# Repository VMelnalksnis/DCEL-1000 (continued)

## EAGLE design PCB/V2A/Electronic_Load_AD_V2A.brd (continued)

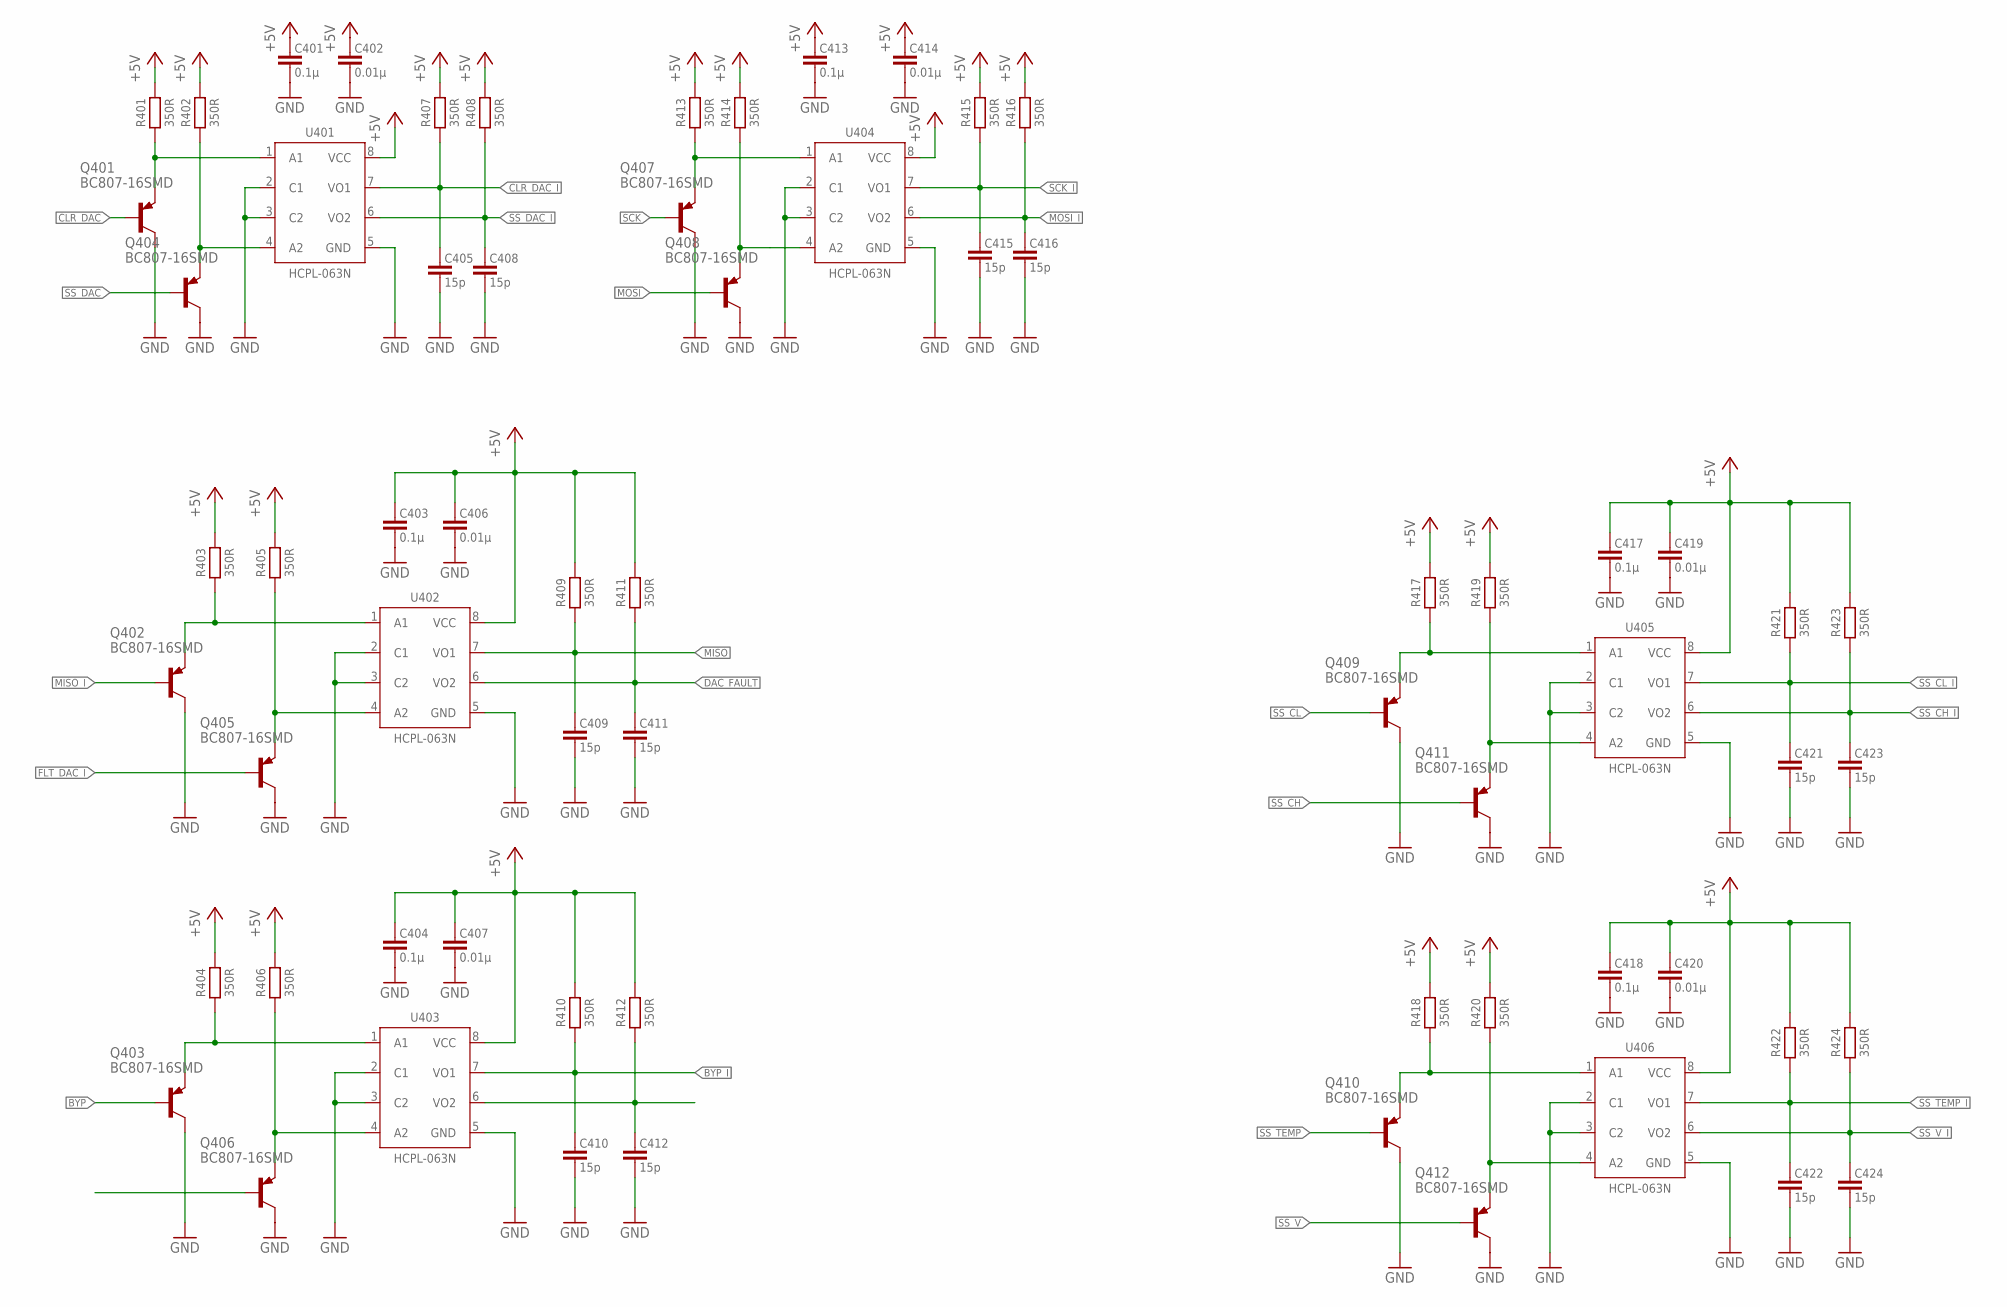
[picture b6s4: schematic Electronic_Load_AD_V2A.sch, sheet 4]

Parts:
C401, C403, C404, C413, C417, C418: 0.1µ; C3216
C402, C406, C407, C414, C419, C420: 0.01µ; C3216
C405, C408, C409, C410, C411, C412, C415, C416, C421, C422, C423, C424: 15p; C1608
Q401, Q402, Q403, Q404, Q405, Q406, Q407, Q408, Q409, Q410, Q411, Q412: BC807-16SMD; SOT23-BEC
R401, R402, R403, R404, R405, R406, R407, R408, R409, R410, R411, R412, R413, R414, R415, R416, R417, R418, R419, R420, R421, R422, R423, R424: 350R; R1608
U401, U402, U403, U404, U405, U406: HCPL-063N; SO8

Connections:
+5V: C401.1, C402.1, C403.1, C404.1, C406.1, C407.1, C413.1, C414.1, C417.1, C418.1, C419.1, C420.1, R401.2, R402.2, R403.2, R404.2, R405.2, R406.2, R407.2, R408.2, R409.2, R410.2, R411.2, R412.2, R413.2, R414.2, R415.2, R416.2, R417.2, R418.2, R419.2, R420.2, R421.2, R422.2, R423.2, R424.2, U401.8 (VCC), U402.8 (VCC), U403.8 (VCC), U404.8 (VCC), U405.8 (VCC), U406.8 (VCC); also elsewhere on the board
BYP: Q403.B
BYP_I: C410.1, R410.1, U403.7 (VO1); also elsewhere on the board
CLR_DAC: Q401.B
CLR_DAC_I: C405.1, R407.1, U401.7 (VO1); also elsewhere on the board
DAC_FAULT: C411.1, R411.1, U402.6 (VO2)
FLT_DAC_I: Q405.B; also elsewhere on the board
GND: C401.2, C402.2, C403.2, C404.2, C405.2, C406.2, C407.2, C408.2, C409.2, C410.2, C411.2, C412.2, C413.2, C414.2, C415.2, C416.2, C417.2, C418.2, C419.2, C420.2, C421.2, C422.2, C423.2, C424.2, Q401.C, Q402.C, Q403.C, Q404.C, Q405.C, Q406.C, Q407.C, Q408.C, Q409.C, Q410.C, Q411.C, Q412.C, U401.2 (C1), U401.3 (C2), U401.5 (GND), U402.2 (C1), U402.3 (C2), U402.5 (GND), U403.2 (C1), U403.3 (C2), U403.5 (GND), U404.2 (C1), U404.3 (C2), U404.5 (GND), U405.2 (C1), U405.3 (C2), U405.5 (GND), U406.2 (C1), U406.3 (C2), U406.5 (GND); also elsewhere on the board
MISO: C409.1, R409.1, U402.7 (VO1)
MISO_I: Q402.B; also elsewhere on the board
MOSI: Q408.B
MOSI_I: C416.1, R416.1, U404.6 (VO2); also elsewhere on the board
unnamed: Q407.E, R413.1, U404.1 (A1)
unnamed: Q409.E, R417.1, U405.1 (A1)
unnamed: Q408.E, R414.1, U404.4 (A2)
unnamed: Q411.E, R419.1, U405.4 (A2)
unnamed: Q410.E, R418.1, U406.1 (A1)
unnamed: Q412.E, R420.1, U406.4 (A2)
unnamed: Q402.E, R403.1, U402.1 (A1)
unnamed: Q405.E, R405.1, U402.4 (A2)
unnamed: Q403.E, R404.1, U403.1 (A1)
unnamed: Q406.E, R406.1, U403.4 (A2)
unnamed: C412.1, R412.1, U403.6 (VO2)
unnamed: Q401.E, R401.1, U401.1 (A1)
unnamed: Q404.E, R402.1, U401.4 (A2)
SCK: Q407.B
SCK_I: C415.1, R415.1, U404.7 (VO1); also elsewhere on the board
SS_CH: Q411.B
SS_CH_I: C423.1, R423.1, U405.6 (VO2); also elsewhere on the board
SS_CL: Q409.B
SS_CL_I: C421.1, R421.1, U405.7 (VO1); also elsewhere on the board
SS_DAC: Q404.B
SS_DAC_I: C408.1, R408.1, U401.6 (VO2); also elsewhere on the board
SS_TEMP: Q410.B
SS_TEMP_I: C422.1, R422.1, U406.7 (VO1); also elsewhere on the board
SS_V: Q412.B
SS_V_I: C424.1, R424.1, U406.6 (VO2); also elsewhere on the board

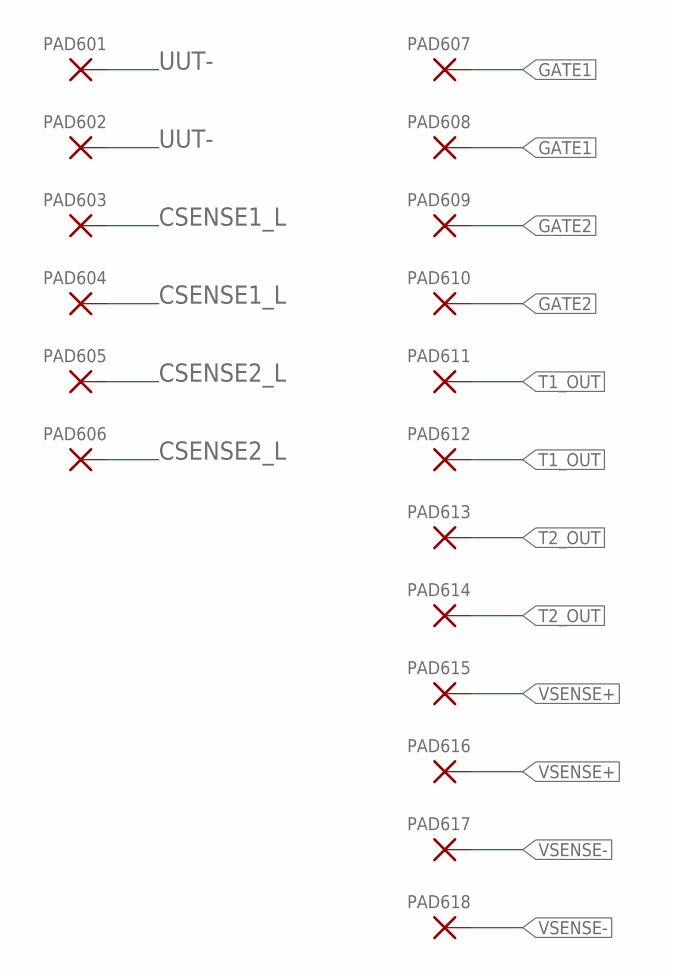
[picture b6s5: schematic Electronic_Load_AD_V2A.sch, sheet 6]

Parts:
PAD601, PAD602, PAD603, PAD604, PAD605, PAD606: PAD-10X4
PAD607, PAD608, PAD609, PAD610, PAD611, PAD612, PAD613, PAD614, PAD615, PAD616, PAD617, PAD618: PAD-5X2

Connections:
CSENSE1_L: PAD603.1, PAD604.1; also elsewhere on the board
CSENSE2_L: PAD605.1, PAD606.1; also elsewhere on the board
GATE1: PAD607.1, PAD608.1; also elsewhere on the board
GATE2: PAD609.1, PAD610.1; also elsewhere on the board
T1_OUT: PAD611.1, PAD612.1; also elsewhere on the board
T2_OUT: PAD613.1, PAD614.1; also elsewhere on the board
UUT-: PAD601.1, PAD602.1; also elsewhere on the board
VSENSE+: PAD615.1, PAD616.1; also elsewhere on the board
VSENSE-: PAD617.1, PAD618.1; also elsewhere on the board

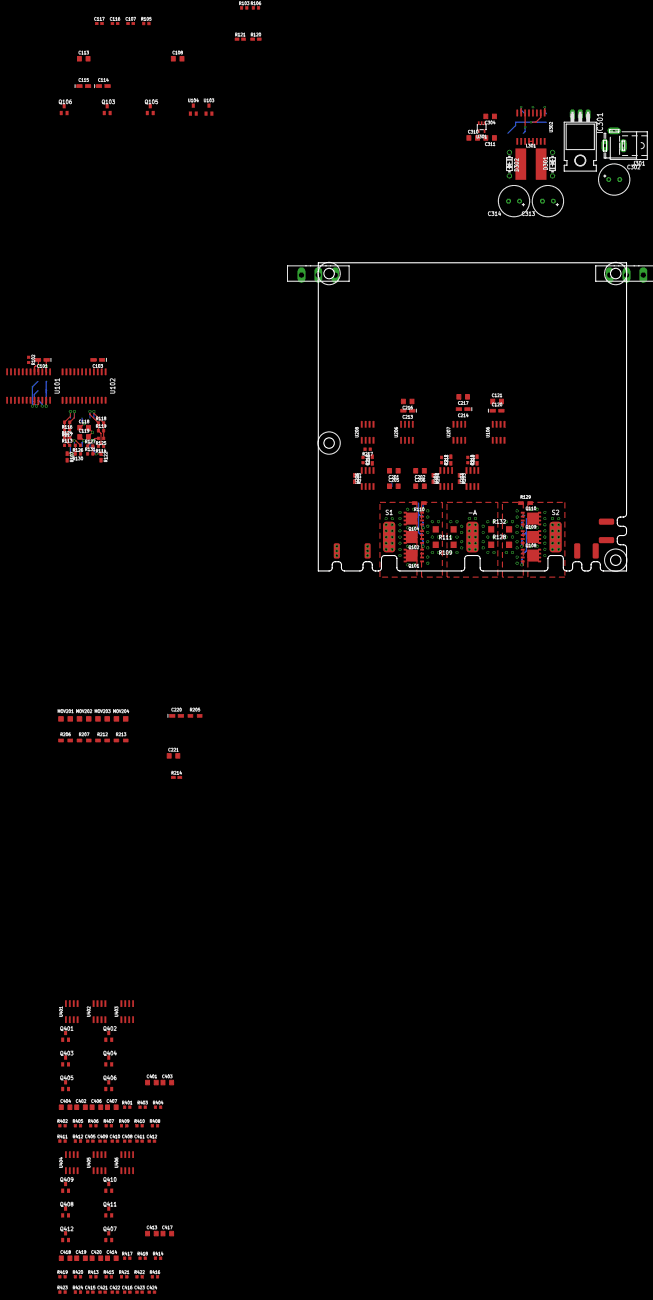
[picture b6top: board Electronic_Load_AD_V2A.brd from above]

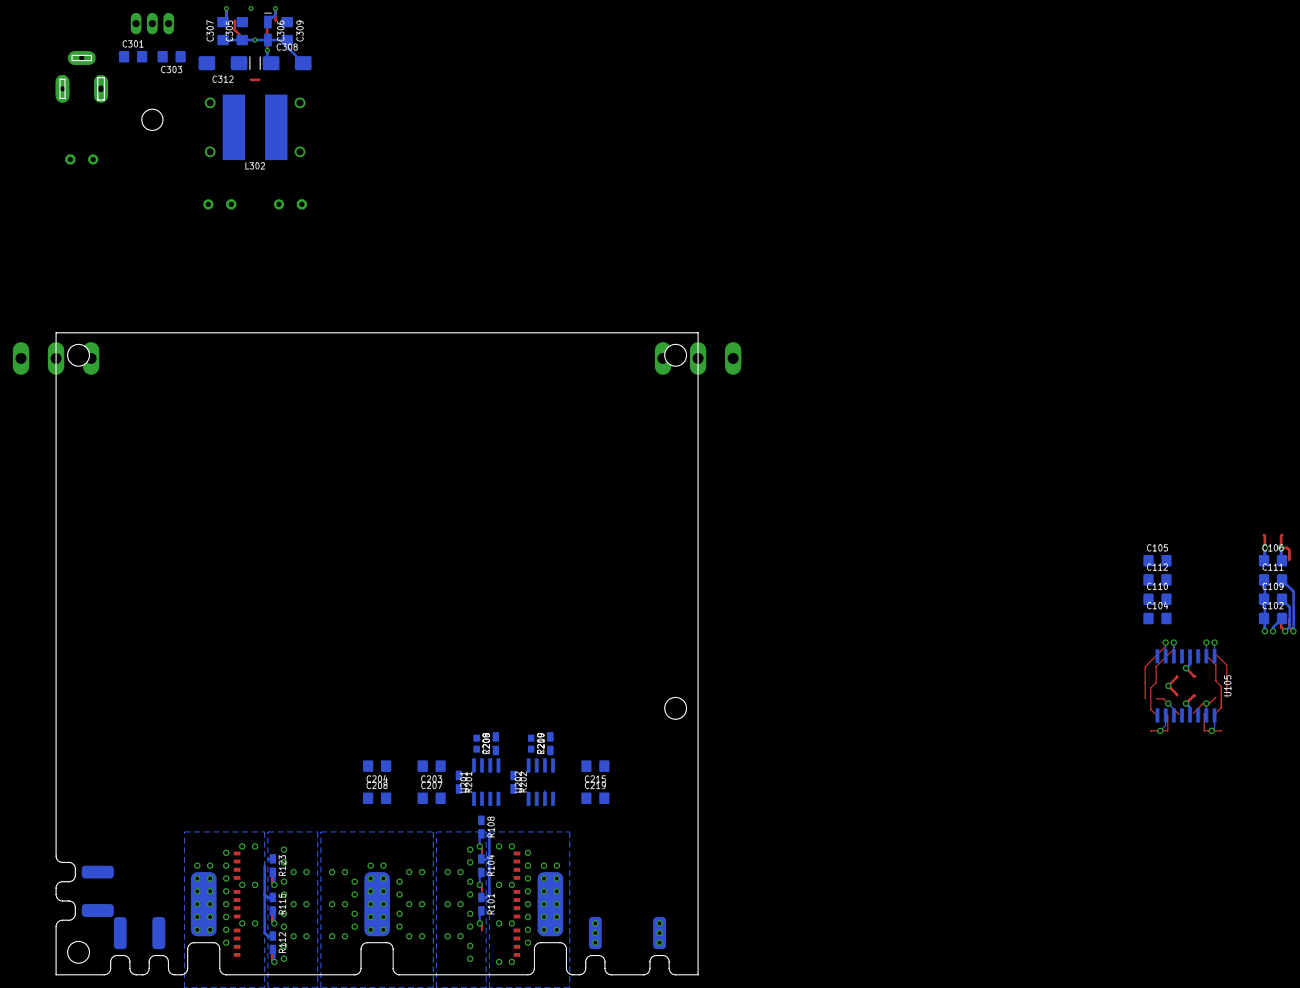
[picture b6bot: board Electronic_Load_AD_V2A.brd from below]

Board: 4 copper layers, 230 parts (47 on the bottom side), 107 nets.

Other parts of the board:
U$1, U$2, U$3, U$4: M3

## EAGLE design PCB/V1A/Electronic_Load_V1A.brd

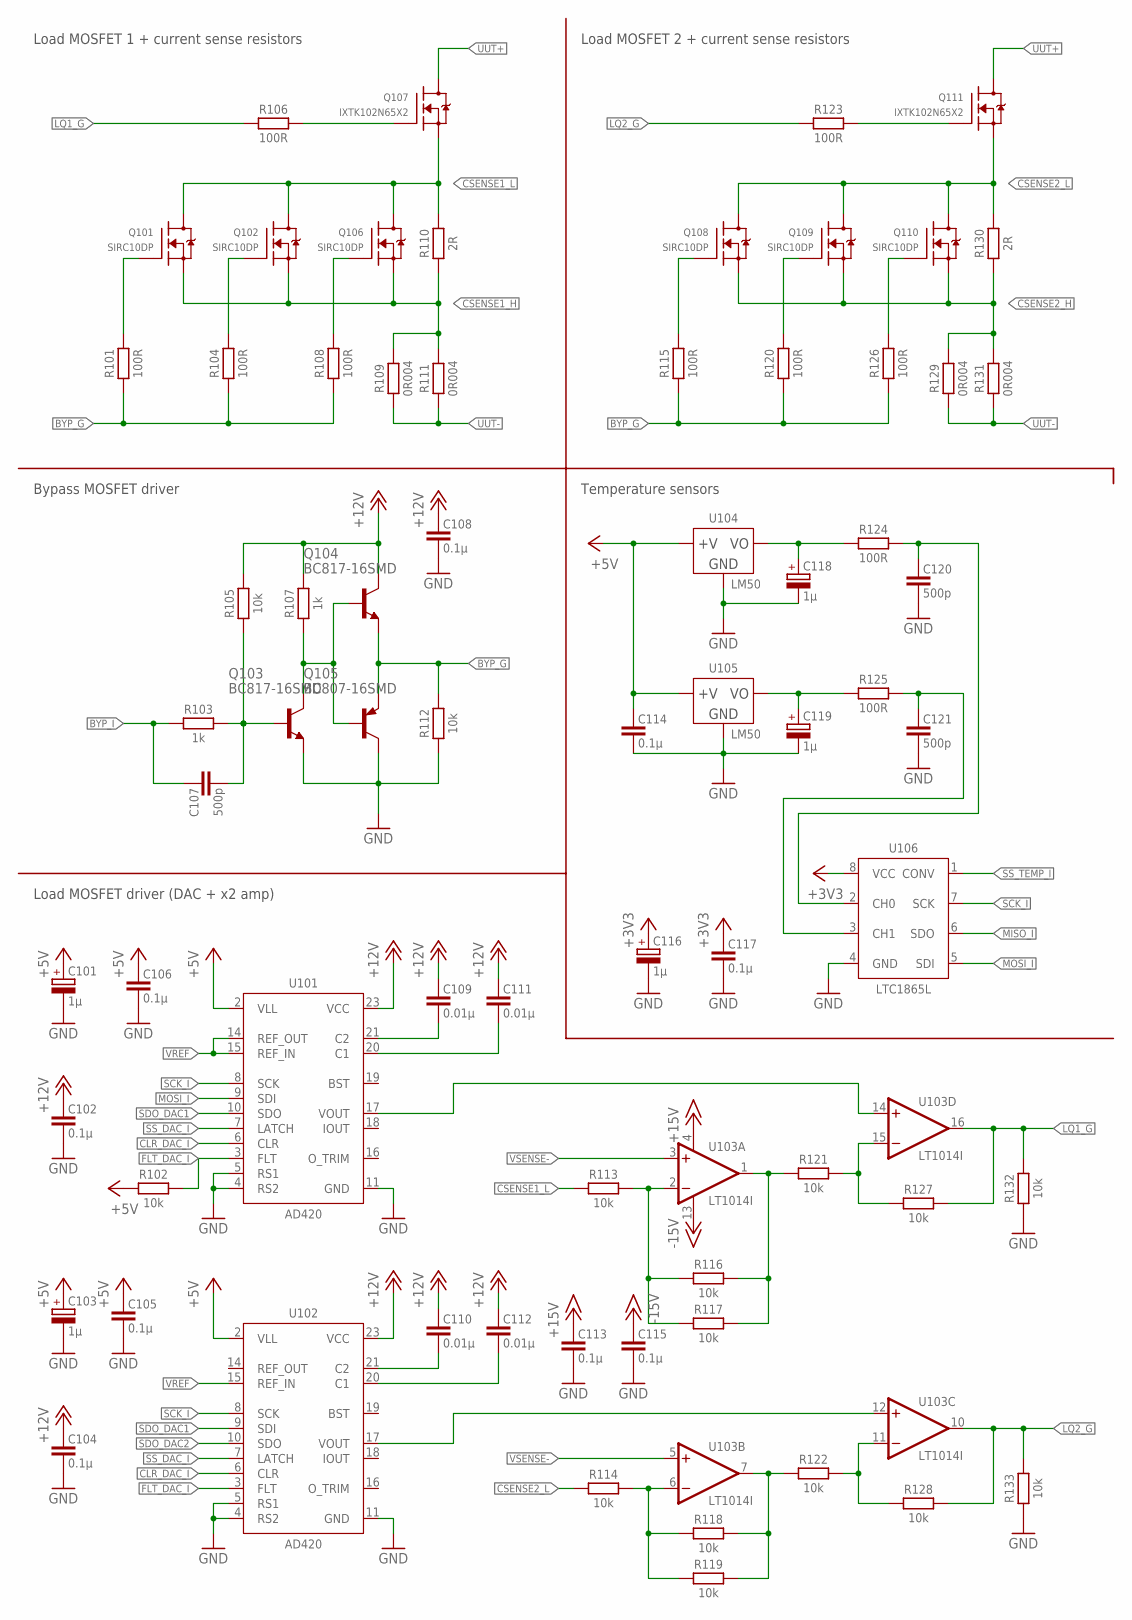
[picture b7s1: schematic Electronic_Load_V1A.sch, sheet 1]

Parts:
C101, C103, C116, C118, C119: 1µ; CT3216
C102, C104, C105, C106, C108, C113, C114, C115, C117: 0.1µ; C3216
C107, C120, C121: 500p; C1608
C109, C110, C111, C112: 0.01µ; C3216
Q101, Q102, Q106, Q108, Q109, Q110: SIRC10DP; POWERPAK-SO-8
Q103, Q104: BC817-16SMD; SOT23-BEC
Q105: BC807-16SMD; SOT23-BEC
R101, R104, R106, R108, R115, R120, R123, R124, R125, R126: 100R; R2012W
R102, R105, R112, R113, R114, R116, R117, R118, R119, R121, R122, R127, R128, R132, R133: 10k; R1608
R103, R107: 1k; R1608
R109, R111, R129, R131: 0R004; R6332W
R110, R130: 2R; R3216W
U101, U102: AD420; SO24W
U103: LT1014I; SO16W
U106: LTC1865L; SO8

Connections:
+3V3: C116.+, C117.1, U106.8 (VCC); also elsewhere on the board
+5V: C101.+, C103.+, C105.1, C106.1, C114.1, R102.1, U101.2 (VLL), U102.2 (VLL); also elsewhere on the board
+12V: C102.1, C104.1, C108.1, C109.1, C110.1, C111.1, C112.1, Q104.C, R105.2, R107.2, U101.23 (VCC), U102.23 (VCC); also elsewhere on the board
+15V: C113.1, U103.4 (V+); also elsewhere on the board
-15V: C115.1, U103.13 (V-); also elsewhere on the board
BYP_G: Q104.E, Q105.E, R101.1, R104.1, R108.1, R112.2, R115.1, R120.1, R126.1
BYP_I: C107.1, R103.1; also elsewhere on the board
CLR_DAC_I: U101.6 (CLR), U102.6 (CLR); also elsewhere on the board
CSENSE1_H: Q101.1 (S), Q101.2 (S), Q101.3 (S), Q102.1 (S), Q102.2 (S), Q102.3 (S), Q106.1 (S), Q106.2 (S), Q106.3 (S), R109.2, R110.1, R111.2; also elsewhere on the board
CSENSE1_L: Q101.5 (D), Q102.5 (D), Q106.5 (D), R110.2, R113.1; also elsewhere on the board
CSENSE2_H: Q108.1 (S), Q108.2 (S), Q108.3 (S), Q109.1 (S), Q109.2 (S), Q109.3 (S), Q110.1 (S), Q110.2 (S), Q110.3 (S), R129.2, R130.1, R131.2; also elsewhere on the board
CSENSE2_L: Q108.5 (D), Q109.5 (D), Q110.5 (D), R114.1, R130.2; also elsewhere on the board
FLT_DAC_I: R102.2, U101.3 (FLT), U102.3 (FLT); also elsewhere on the board
GATE1: R106.2; also elsewhere on the board
GATE2: R123.2; also elsewhere on the board
GND: C101.-, C102.2, C103.-, C104.2, C105.2, C106.2, C108.2, C113.2, C114.2, C115.2, C116.-, C117.2, C118.-, C119.-, C120.2, C121.2, Q103.E, Q105.C, R112.1, R132.1, R133.1, U101.4 (RS2), U101.5 (RS1), U101.11 (GND), U102.4 (RS2), U102.5 (RS1), U102.11 (GND), U106.4 (GND); also elsewhere on the board
LBQ11_G: Q101.4 (G), R101.2
LBQ12_G: Q102.4 (G), R104.2
LBQ13_G: Q106.4 (G), R108.2
LBQ21_G: Q108.4 (G), R115.2
LBQ22_G: Q109.4 (G), R120.2
LBQ23_G: Q110.4 (G), R126.2
LQ1_G: R106.1, R127.2, R132.2, U103.16 (OUT)
LQ2_G: R123.1, R128.2, R133.2, U103.10 (OUT)
MISO_I: U106.6 (SDO); also elsewhere on the board
MOSI_I: U101.9 (SDI), U106.5 (SDI); also elsewhere on the board
unnamed: C109.2, U101.21 (C2)
unnamed: C111.2, U101.20 (C1)
unnamed: Q103.C, Q104.B, Q105.B, R107.1
unnamed: C110.2, U102.21 (C2)
unnamed: C112.2, U102.20 (C1)
unnamed: C107.2, Q103.B, R103.2, R105.1
unnamed: R122.2, R128.1, U103.11 (-IN)
unnamed: U101.17 (VOUT), U103.14 (+IN)
unnamed: U102.17 (VOUT), U103.12 (+IN)
unnamed: R121.2, R127.1, U103.15 (-IN)
unnamed: R116.2, R117.2, R121.1, U103.1 (OUT)
unnamed: R113.2, R116.1, R117.1, U103.2 (-IN)
unnamed: R114.2, R118.1, R119.1, U103.6 (-IN)
unnamed: R118.2, R119.2, R122.1, U103.7 (OUT)
SCK_I: U101.8 (SCK), U102.8 (SCK), U106.7 (SCK); also elsewhere on the board
SDO_DAC1: U101.10 (SDO), U102.9 (SDI)
SDO_DAC2: U102.10 (SDO)
SS_DAC_I: U101.7 (LATCH), U102.7 (LATCH); also elsewhere on the board
SS_TEMP_I: U106.1 (CONV); also elsewhere on the board
T1_OUT: C118.+, R124.1; also elsewhere on the board
T2_OUT: C119.+, R125.1; also elsewhere on the board
TEMP1: C120.1, R124.2, U106.2 (CH0)
TEMP2: C121.1, R125.2, U106.3 (CH1)
UUT-: R109.1, R111.1, R129.1, R131.1; also elsewhere on the board
VREF: U101.14 (REF_OUT), U101.15 (REF_IN), U102.15 (REF_IN); also elsewhere on the board
VSENSE-: U103.3 (+IN), U103.5 (+IN); also elsewhere on the board

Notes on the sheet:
Load MOSFET 1 + current sense resistors
Load MOSFET 2 + current sense resistors
Bypass MOSFET driver
Load MOSFET driver (DAC + x2 amp)
Temperature sensors

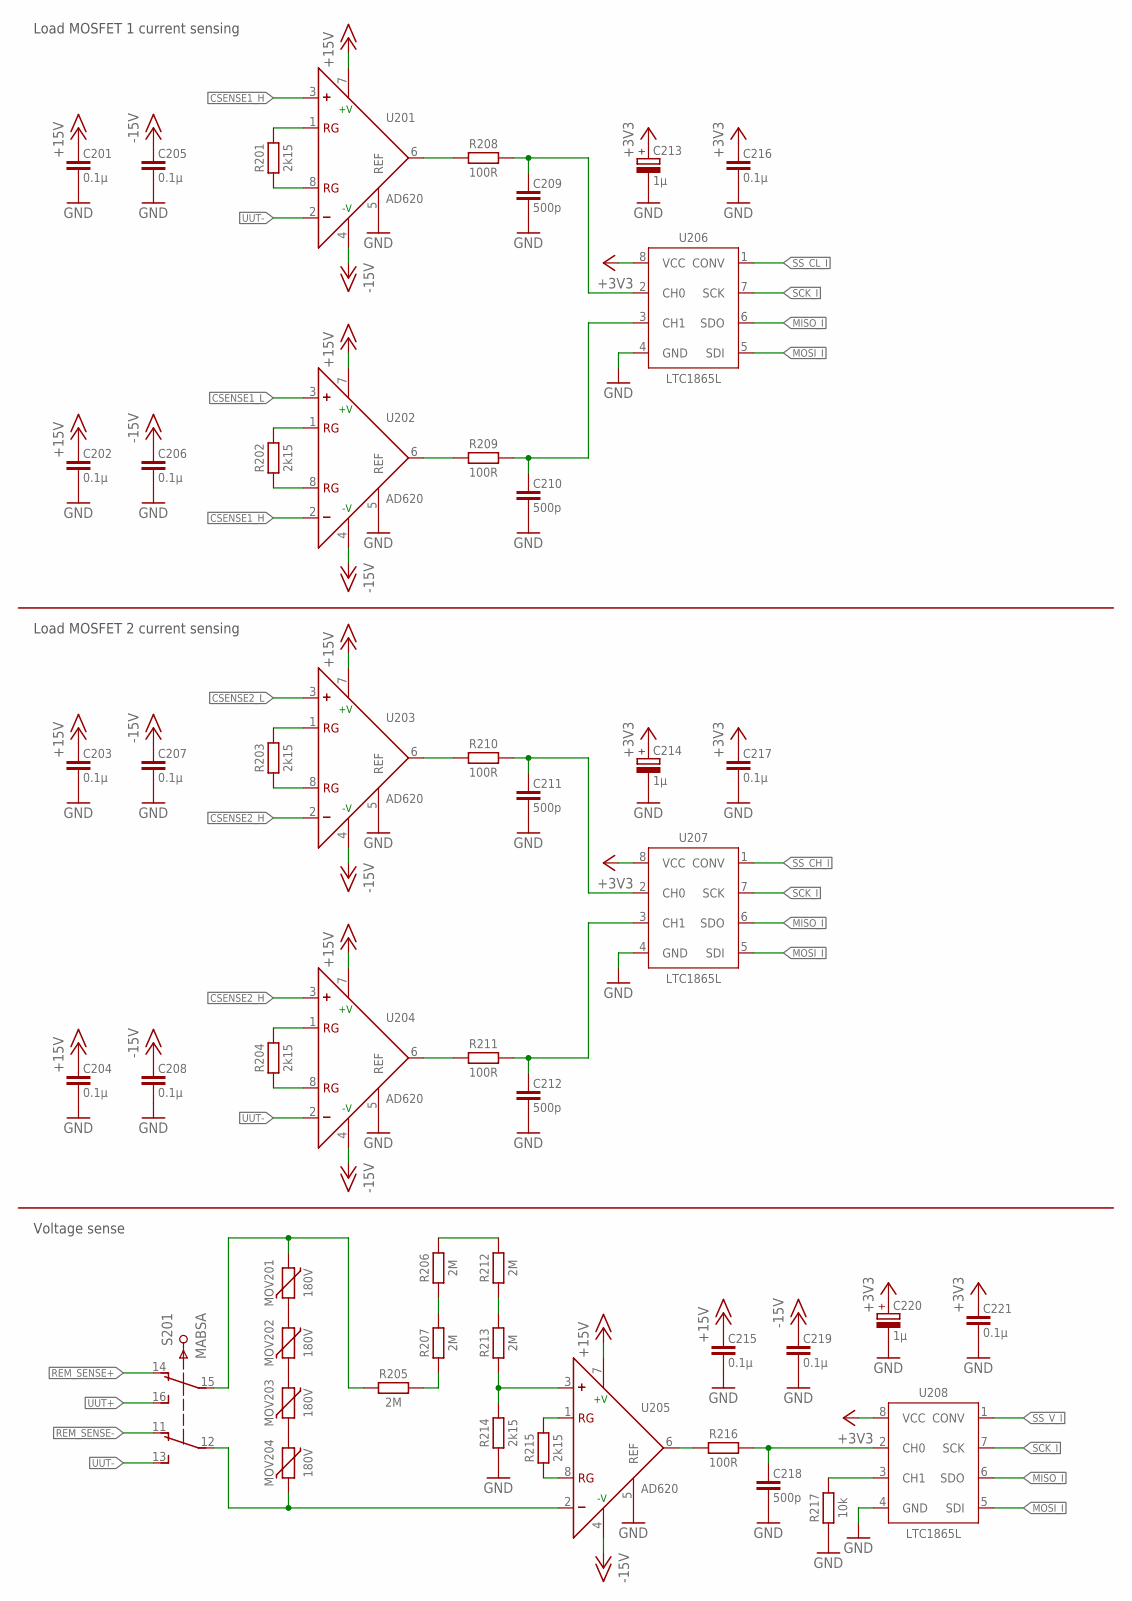
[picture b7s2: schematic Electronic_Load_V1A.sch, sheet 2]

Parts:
C201, C202, C203, C204, C205, C206, C207, C208, C215, C216, C217, C219, C221: 0.1µ; C3216
C209, C210, C211, C212, C218: 500p; C1608
C213, C214, C220: 1µ; CT3216
MOV201, MOV202, MOV203, MOV204: 180V; R3225W
R201, R202, R203, R204, R214, R215: 2k15; R2012W
R205, R206, R207, R212, R213: 2M; R3216W
R208, R209, R210, R211, R216: 100R; R2012W
R217: 10k; R1608
S201: MABSA
U201, U202, U203, U204, U205: AD620; SO8
U206, U207, U208: LTC1865L; SO8

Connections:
+3V3: C213.+, C214.+, C216.1, C217.1, C220.+, C221.1, U206.8 (VCC), U207.8 (VCC), U208.8 (VCC); also elsewhere on the board
+15V: C201.1, C202.1, C203.1, C204.1, C215.1, U201.7 (+V), U202.7 (+V), U203.7 (+V), U204.7 (+V), U205.7 (+V); also elsewhere on the board
-15V: C205.1, C206.1, C207.1, C208.1, C219.1, U201.4 (-V), U202.4 (-V), U203.4 (-V), U204.4 (-V), U205.4 (-V); also elsewhere on the board
CSENSE1_H: U201.3 (+), U202.2 (-); also elsewhere on the board
CSENSE1_L: U202.3 (+); also elsewhere on the board
CSENSE2_H: U203.2 (-), U204.3 (+); also elsewhere on the board
CSENSE2_L: U203.3 (+); also elsewhere on the board
GND: C201.2, C202.2, C203.2, C204.2, C205.2, C206.2, C207.2, C208.2, C209.2, C210.2, C211.2, C212.2, C213.-, C214.-, C215.2, C216.2, C217.2, C218.2, C219.2, C220.-, C221.2, R214.1, R217.1, U201.5 (REF), U202.5 (REF), U203.5 (REF), U204.5 (REF), U205.5 (REF), U206.4 (GND), U207.4 (GND), U208.4 (GND); also elsewhere on the board
MISO_I: U206.6 (SDO), U207.6 (SDO), U208.6 (SDO); also elsewhere on the board
MOSI_I: U206.5 (SDI), U207.5 (SDI), U208.5 (SDI); also elsewhere on the board
unnamed: MOV201.2, MOV202.1
unnamed: MOV202.2, MOV203.1
unnamed: R210.1, U203.6 (OUT)
unnamed: C211.1, R210.2, U207.2 (CH0)
unnamed: R211.1, U204.6 (OUT)
unnamed: C212.1, R211.2, U207.3 (CH1)
unnamed: C209.1, R208.2, U206.2 (CH0)
unnamed: C210.1, R209.2, U206.3 (CH1)
unnamed: R209.1, U202.6 (OUT)
unnamed: R208.1, U201.6 (OUT)
unnamed: R212.1, R213.2
unnamed: R206.2, R212.2
unnamed: R206.1, R207.2
unnamed: R205.2, R207.1
unnamed: R213.1, R214.2, U205.3 (+)
unnamed: C218.1, R216.2, U208.2 (CH0)
unnamed: R216.1, U205.6 (OUT)
unnamed: MOV203.2, MOV204.1
unnamed: R217.2, U208.3 (CH1)
REM_SENSE+: S201.14
REM_SENSE-: S201.11
RG1_H4: R203.2, U203.1 (RG)
RG1_H5: R204.2, U204.1 (RG)
RG1_H6: R215.2, U205.1 (RG)
RG1_L3: R201.2, U201.1 (RG)
RG1_L4: R202.2, U202.1 (RG)
RG2_H4: R203.1, U203.8 (RG)
RG2_H5: R204.1, U204.8 (RG)
RG2_H6: R215.1, U205.8 (RG)
RG2_L3: R201.1, U201.8 (RG)
RG2_L4: R202.1, U202.8 (RG)
SCK_I: U206.7 (SCK), U207.7 (SCK), U208.7 (SCK); also elsewhere on the board
SS_CH_I: U207.1 (CONV); also elsewhere on the board
SS_CL_I: U206.1 (CONV); also elsewhere on the board
SS_V_I: U208.1 (CONV); also elsewhere on the board
UUT+: S201.16
UUT-: S201.13, U201.2 (-), U204.2 (-); also elsewhere on the board
VSENSE+: MOV201.1, R205.1, S201.15; also elsewhere on the board
VSENSE-: MOV204.2, S201.12, U205.2 (-); also elsewhere on the board

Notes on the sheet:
Load MOSFET 2 current sensing
Load MOSFET 1 current sensing
Voltage sense

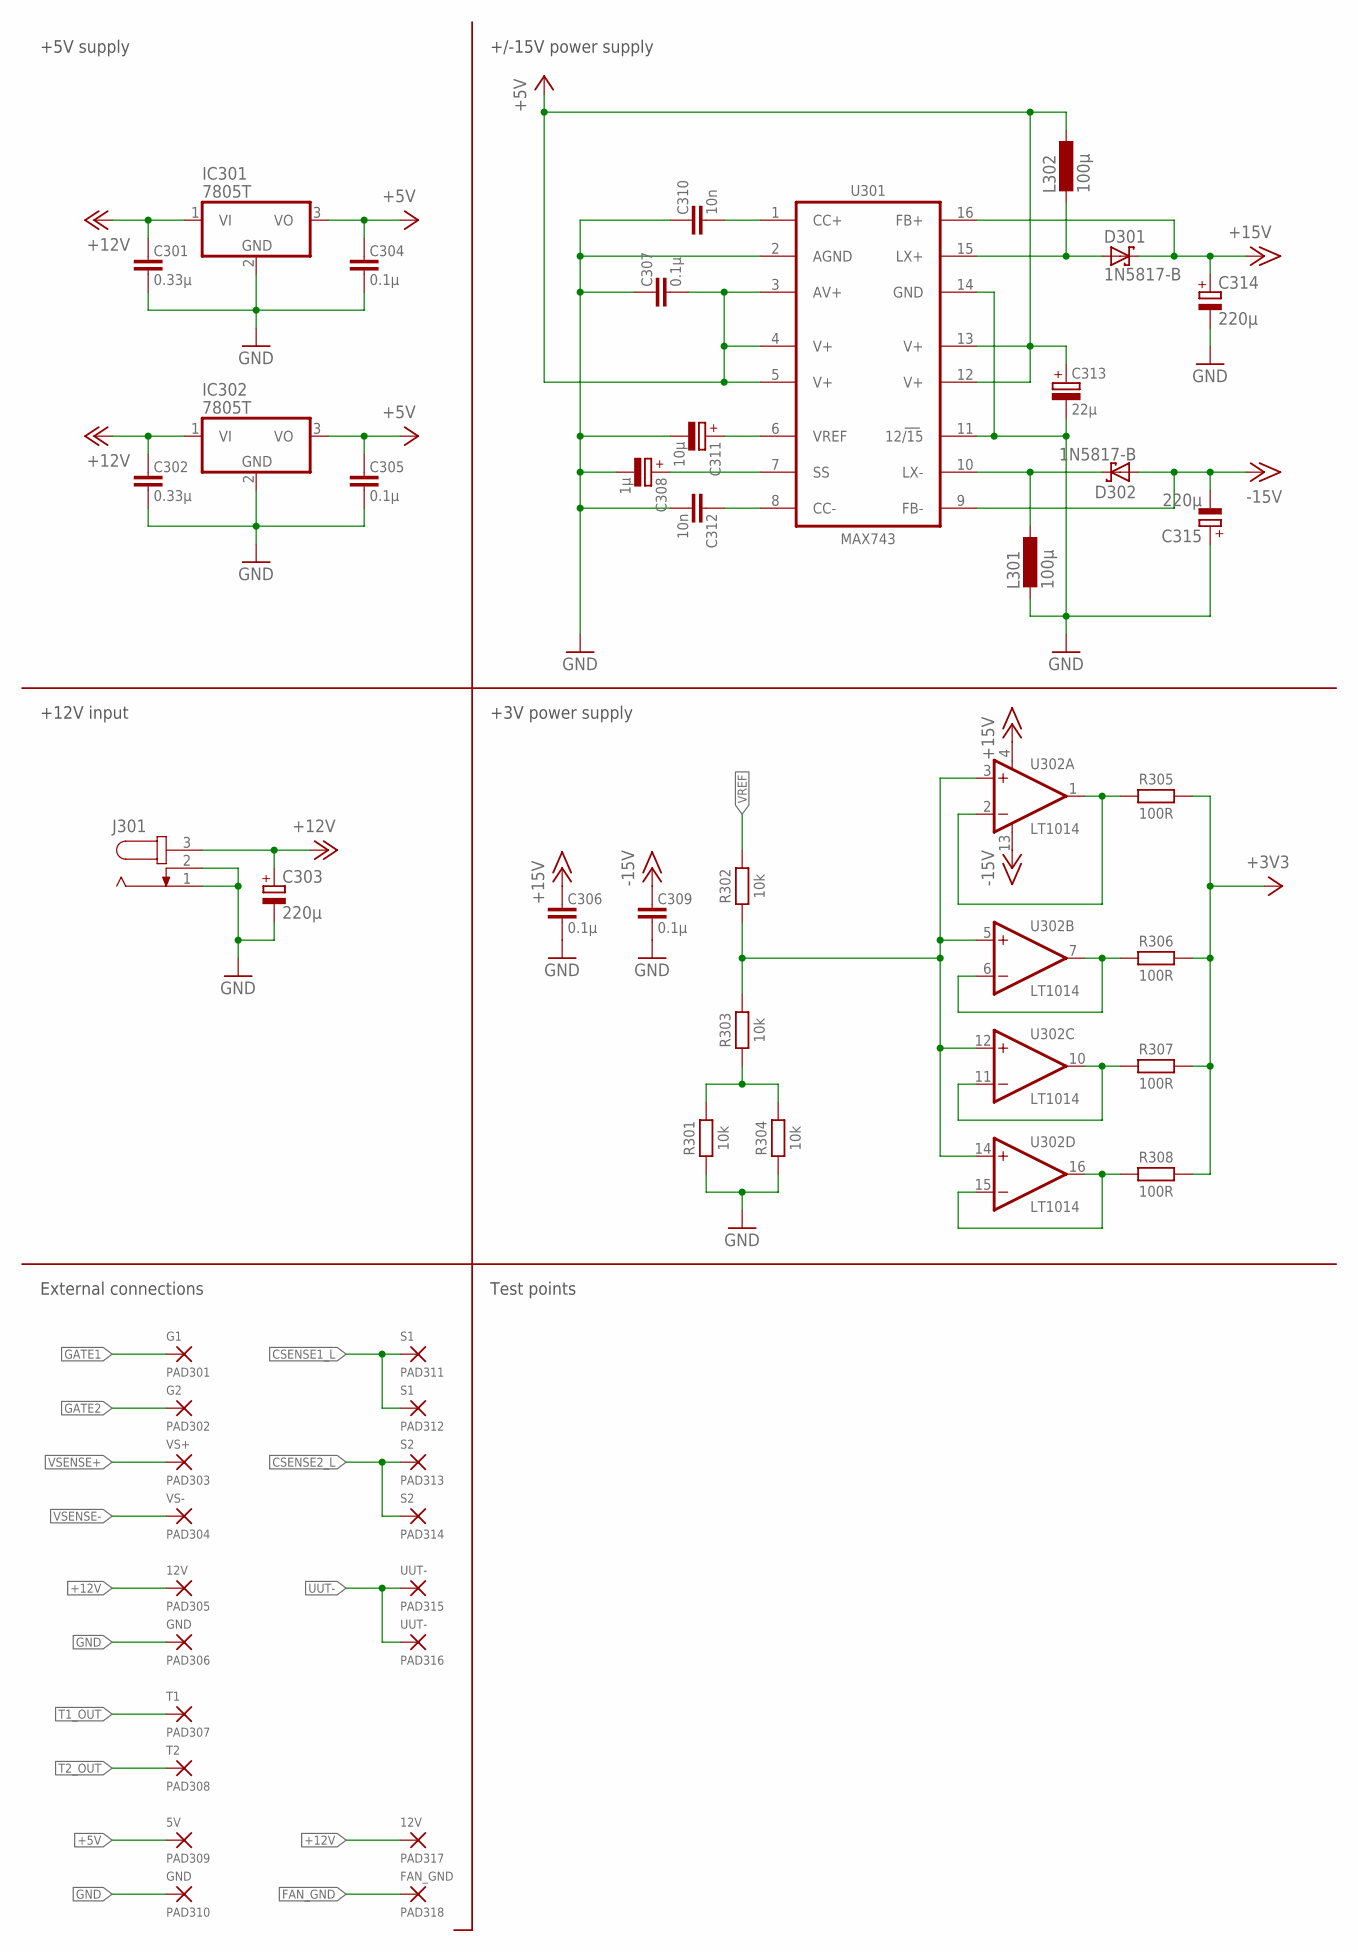
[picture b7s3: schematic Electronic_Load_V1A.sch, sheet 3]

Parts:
C301, C302: 0.33µ; C3216
C303, C314, C315: 220µ; E3,5-10
C304, C305, C306, C307, C309: 0.1µ; C3216
C308: 1µ; CT3216
C310, C312: 10n; C3216
C311: 10µ; CT6032
C313: 22µ; CT6032
D301, D302: 1N5817-B; DO41-7.6
IC301, IC302: 7805T; TO220H
J301: JACK-PLUG0; SPC4077
L301, L302: 100µ; 0204/5
PAD301: G1; PAD-5X2
PAD302: G2; PAD-5X2
PAD303: VS+; PAD-5X2
PAD304: VS-; PAD-5X2
PAD305, PAD317: 12V; PAD-5X2
PAD306, PAD310: GND; PAD-5X2
PAD307: T1; PAD-5X2
PAD308: T2; PAD-5X2
PAD309: 5V; PAD-5X2
PAD311, PAD312: S1; PAD-10X4
PAD313, PAD314: S2; PAD-10X4
PAD315, PAD316: UUT-; PAD-10X4
PAD318: FAN_GND; PAD-5X2
R301, R302, R303, R304: 10k; R1608
R305, R306, R307, R308: 100R; R2012W
U301: MAX743; SO16W
U302: LT1014; SO16W

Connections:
+3V3: R305.2, R306.2, R307.2, R308.2; also elsewhere on the board
+5V: C304.1, C305.1, C307.2, C313.+, IC301.3 (VO), IC302.3 (VO), L302.1, PAD309.1, U301.3 (AV+), U301.4 (V+), U301.5 (V+), U301.12 (V+), U301.13 (V+); also elsewhere on the board
+12V: C301.1, C302.1, C303.+, IC301.1 (VI), IC302.1 (VI), J301.3, PAD305.1, PAD317.1; also elsewhere on the board
+15V: C306.1, C314.+, D301.C, U301.16 (FB+), U302.4 (V+); also elsewhere on the board
-15V: C309.1, C315.-, D302.A, U301.9 (FB-), U302.13 (V-); also elsewhere on the board
CSENSE1_L: PAD311.1, PAD312.1; also elsewhere on the board
CSENSE2_L: PAD313.1, PAD314.1; also elsewhere on the board
FAN_GND: PAD318.1; also elsewhere on the board
GATE1: PAD301.1; also elsewhere on the board
GATE2: PAD302.1; also elsewhere on the board
GND: C301.2, C302.2, C303.-, C304.2, C305.2, C306.2, C307.1, C308.-, C309.2, C310.1, C311.-, C312.2, C313.-, C314.-, C315.+, IC301.2 (GND), IC302.2 (GND), J301.1, J301.2, L301.2, PAD306.1, PAD310.1, R301.1, R304.1, U301.2 (AGND), U301.11 (12/15), U301.14 (GND); also elsewhere on the board
unnamed: C312.1, U301.8 (CC-)
unnamed: C308.+, U301.7 (SS)
unnamed: C310.2, U301.1 (CC+)
unnamed: D301.A, L302.2, U301.15 (LX+)
unnamed: R302.1, R303.2, U302.3 (+IN), U302.5 (+IN), U302.12 (+IN), U302.14 (+IN)
unnamed: R306.1, U302.6 (-IN), U302.7 (OUT)
unnamed: R305.1, U302.1 (OUT), U302.2 (-IN)
unnamed: R307.1, U302.10 (OUT), U302.11 (-IN)
unnamed: D302.C, L301.1, U301.10 (LX-)
unnamed: R308.1, U302.15 (-IN), U302.16 (OUT)
unnamed: R301.2, R303.1, R304.2
T1_OUT: PAD307.1; also elsewhere on the board
T2_OUT: PAD308.1; also elsewhere on the board
UUT-: PAD315.1, PAD316.1; also elsewhere on the board
VREF: R302.2; also elsewhere on the board
VREF2: C311.+, U301.6 (VREF)
VSENSE+: PAD303.1; also elsewhere on the board
VSENSE-: PAD304.1; also elsewhere on the board

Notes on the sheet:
+/-15V power supply
+5V supply
+12V input
+3V power supply
External connections
Test points

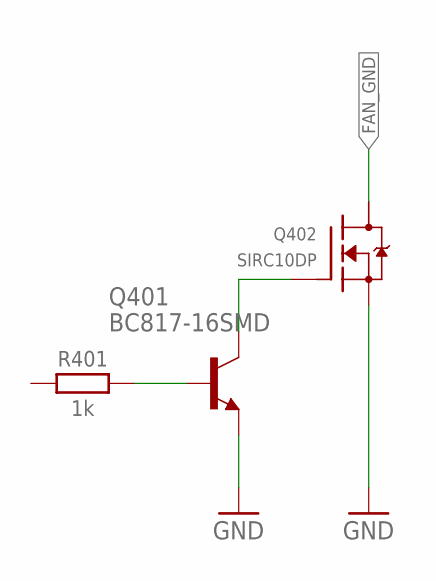
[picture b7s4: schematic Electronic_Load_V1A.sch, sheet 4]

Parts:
Q401: BC817-16SMD; SOT23-BEC
Q402: SIRC10DP; POWERPAK-SO-8
R401: 1k; R1608

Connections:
FAN_GND: Q402.5 (D); also elsewhere on the board
GND: Q401.E, Q402.1 (S), Q402.2 (S), Q402.3 (S); also elsewhere on the board
unnamed: Q401.C, Q402.4 (G)
unnamed: Q401.B, R401.2
